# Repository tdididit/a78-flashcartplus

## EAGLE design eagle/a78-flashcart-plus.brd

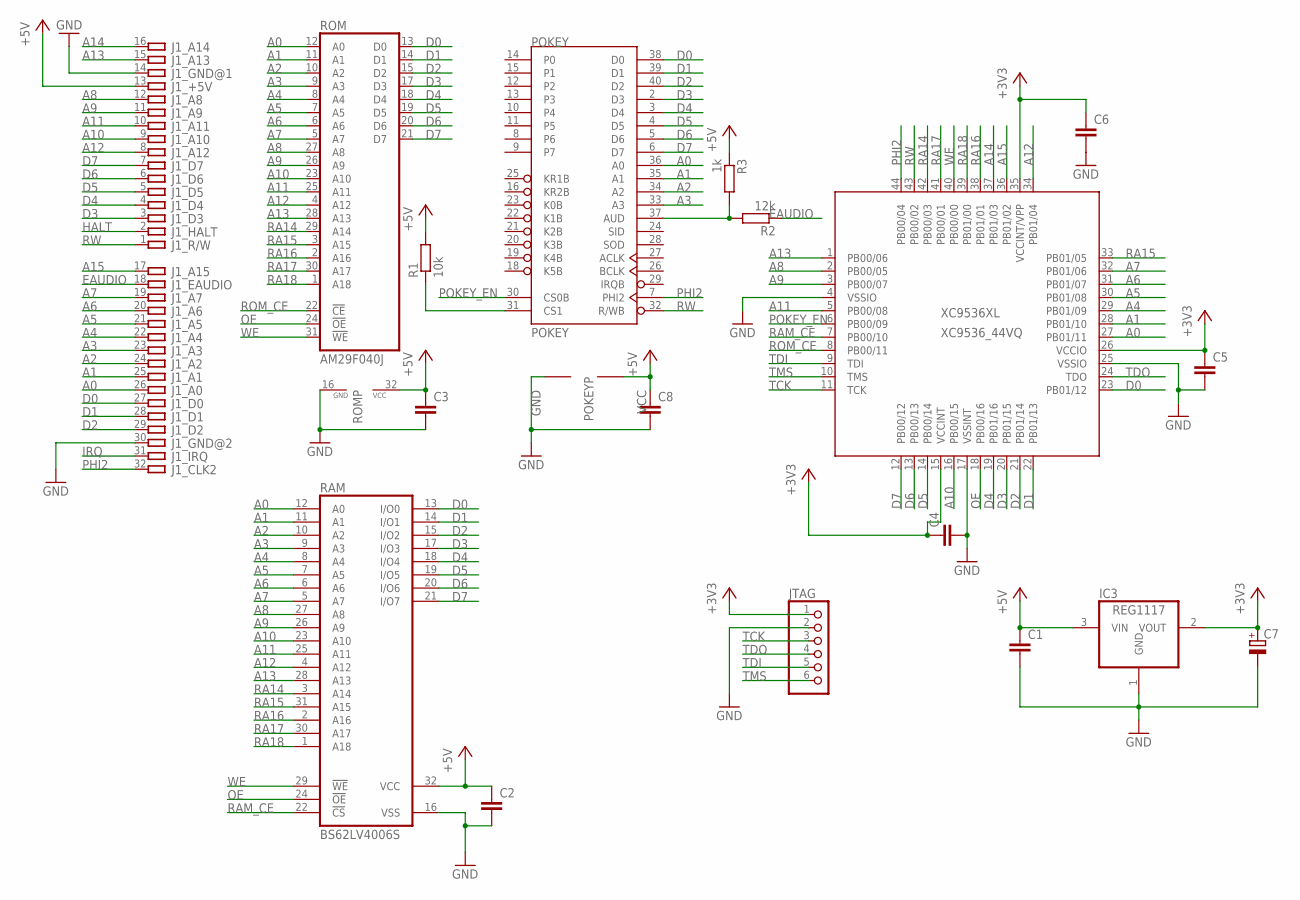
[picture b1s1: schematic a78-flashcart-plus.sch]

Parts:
C1, C2, C3, C4, C5, C6, C8: C-EUC0603; C0603
C7: CPOL-EUSMCC; SMC_C
IC3: REG1117; SOT223
J1: ATARI-7800-LARGE
JTAG: PINHD-1X6; 1X06
POKEY: POKEY; DIL40
R1: 10k; R0603
R2: 12k; R0603
R3: 1k; R0603
RAM: BS62LV4006S; SOP-32
ROM: AM29F040J; PLCC32R
XC9536XL: XC9536_44VQ; SQFP-S-10X10-44

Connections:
+3V3: C4.1, C5.1, C6.1, C7.+, IC3.2 (VOUT), JTAG.1, XC9536XL.15 (VCCINT), XC9536XL.26 (VCCIO), XC9536XL.35 (VCCINT/VPP)
+5V: C1.1, C2.1, C3.1, C8.1, IC3.3 (VIN), J1.13, POKEY.17 (VCC), R1.2, R3.1, RAM.32 (VCC), ROM.32 (VCC)
A0: J1.26, POKEY.36 (A0), RAM.12 (A0), ROM.12 (A0), XC9536XL.27 (PB01/11)
A1: J1.25, POKEY.35 (A1), RAM.11 (A1), ROM.11 (A1), XC9536XL.28 (PB01/10)
A2: J1.24, POKEY.34 (A2), RAM.10 (A2), ROM.10 (A2)
A3: J1.23, POKEY.33 (A3), RAM.9 (A3), ROM.9 (A3)
A4: J1.22, RAM.8 (A4), ROM.8 (A4), XC9536XL.29 (PB01/09)
A5: J1.21, RAM.7 (A5), ROM.7 (A5), XC9536XL.30 (PB01/08)
A6: J1.20, RAM.6 (A6), ROM.6 (A6), XC9536XL.31 (PB01/07)
A7: J1.19, RAM.5 (A7), ROM.5 (A7), XC9536XL.32 (PB01/06)
A8: J1.12, RAM.27 (A8), ROM.27 (A8), XC9536XL.2 (PB00/05)
A9: J1.11, RAM.26 (A9), ROM.26 (A9), XC9536XL.3 (PB00/07)
A10: J1.9, RAM.23 (A10), ROM.23 (A10), XC9536XL.16 (PB00/15)
A11: J1.10, RAM.25 (A11), ROM.25 (A11), XC9536XL.5 (PB00/08)
A12: J1.8, RAM.4 (A12), ROM.4 (A12), XC9536XL.34 (PB01/04)
A13: J1.15, RAM.28 (A13), ROM.28 (A13), XC9536XL.1 (PB00/06)
A14: J1.16, XC9536XL.37 (PB01/03)
A15: J1.17, XC9536XL.36 (PB01/02)
D0: J1.27, POKEY.38 (D0), RAM.13 (I/O0), ROM.13 (D0), XC9536XL.23 (PB01/12)
D1: J1.28, POKEY.39 (D1), RAM.14 (I/O1), ROM.14 (D1), XC9536XL.22 (PB01/13)
D2: J1.29, POKEY.40 (D2), RAM.15 (I/O2), ROM.15 (D2), XC9536XL.21 (PB01/14)
D3: J1.3, POKEY.2 (D3), RAM.17 (I/O3), ROM.17 (D3), XC9536XL.20 (PB01/15)
D4: J1.4, POKEY.3 (D4), RAM.18 (I/O4), ROM.18 (D4), XC9536XL.19 (PB01/16)
D5: J1.5, POKEY.4 (D5), RAM.19 (I/O5), ROM.19 (D5), XC9536XL.14 (PB00/14)
D6: J1.6, POKEY.5 (D6), RAM.20 (I/O6), ROM.20 (D6), XC9536XL.13 (PB00/13)
D7: J1.7, POKEY.6 (D7), RAM.21 (I/O7), ROM.21 (D7), XC9536XL.12 (PB00/12)
DJGJGFJG: POKEY.31 (CS1), R1.1
EAUDIO: J1.18, R2.1
GND: C1.2, C2.2, C3.2, C4.2, C5.2, C6.2, C7.-, C8.2, IC3.1 (GND), J1.14, J1.30, JTAG.2, POKEY.1 (GND), RAM.16 (VSS), ROM.16 (GND), XC9536XL.4 (VSSIO), XC9536XL.17 (VSSINT), XC9536XL.25 (VSSIO)
HALT: J1.2
IRQ: J1.31
unnamed: POKEY.37 (AUD), R2.2, R3.2
OE: RAM.24 (!OE), ROM.24 (!OE), XC9536XL.18 (PB00/16)
PHI2: J1.32, POKEY.7 (PHI2), XC9536XL.44 (PB00/04)
POKEY_EN: POKEY.30 (CS0B), XC9536XL.6 (PB00/09)
RA14: RAM.3 (A14), ROM.29 (A14), XC9536XL.42 (PB00/03)
RA15: RAM.31 (A15), ROM.3 (A15), XC9536XL.33 (PB01/05)
RA16: RAM.2 (A16), ROM.2 (A16), XC9536XL.38 (PB01/01)
RA17: RAM.30 (A17), ROM.30 (A17), XC9536XL.41 (PB00/01)
RA18: RAM.1 (A18), ROM.1 (A18), XC9536XL.39 (PB01/00)
RAM_CE: RAM.22 (!CS), XC9536XL.7 (PB00/10)
ROM_CE: ROM.22 (!CE), XC9536XL.8 (PB00/11)
RW: J1.1, POKEY.32 (R/WB), XC9536XL.43 (PB00/02)
TCK: JTAG.3, XC9536XL.11 (TCK)
TDI: JTAG.5, XC9536XL.9 (TDI)
TDO: JTAG.4, XC9536XL.24 (TDO)
TMS: JTAG.6, XC9536XL.10 (TMS)
WE: RAM.29 (!WE), ROM.31 (!WE), XC9536XL.40 (PB00/00)

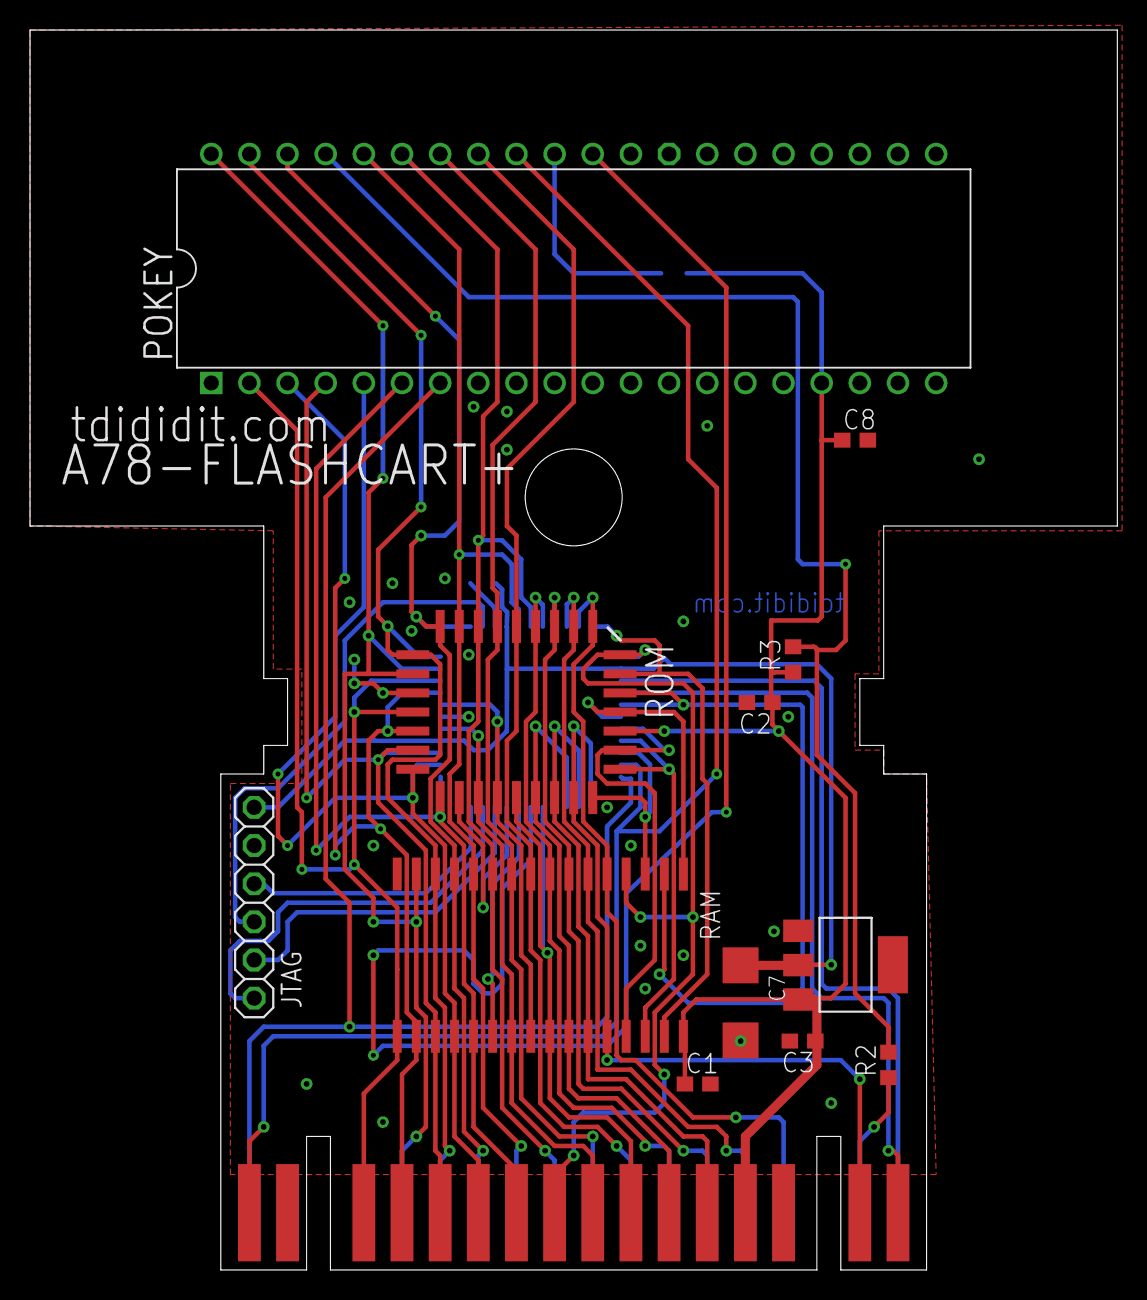
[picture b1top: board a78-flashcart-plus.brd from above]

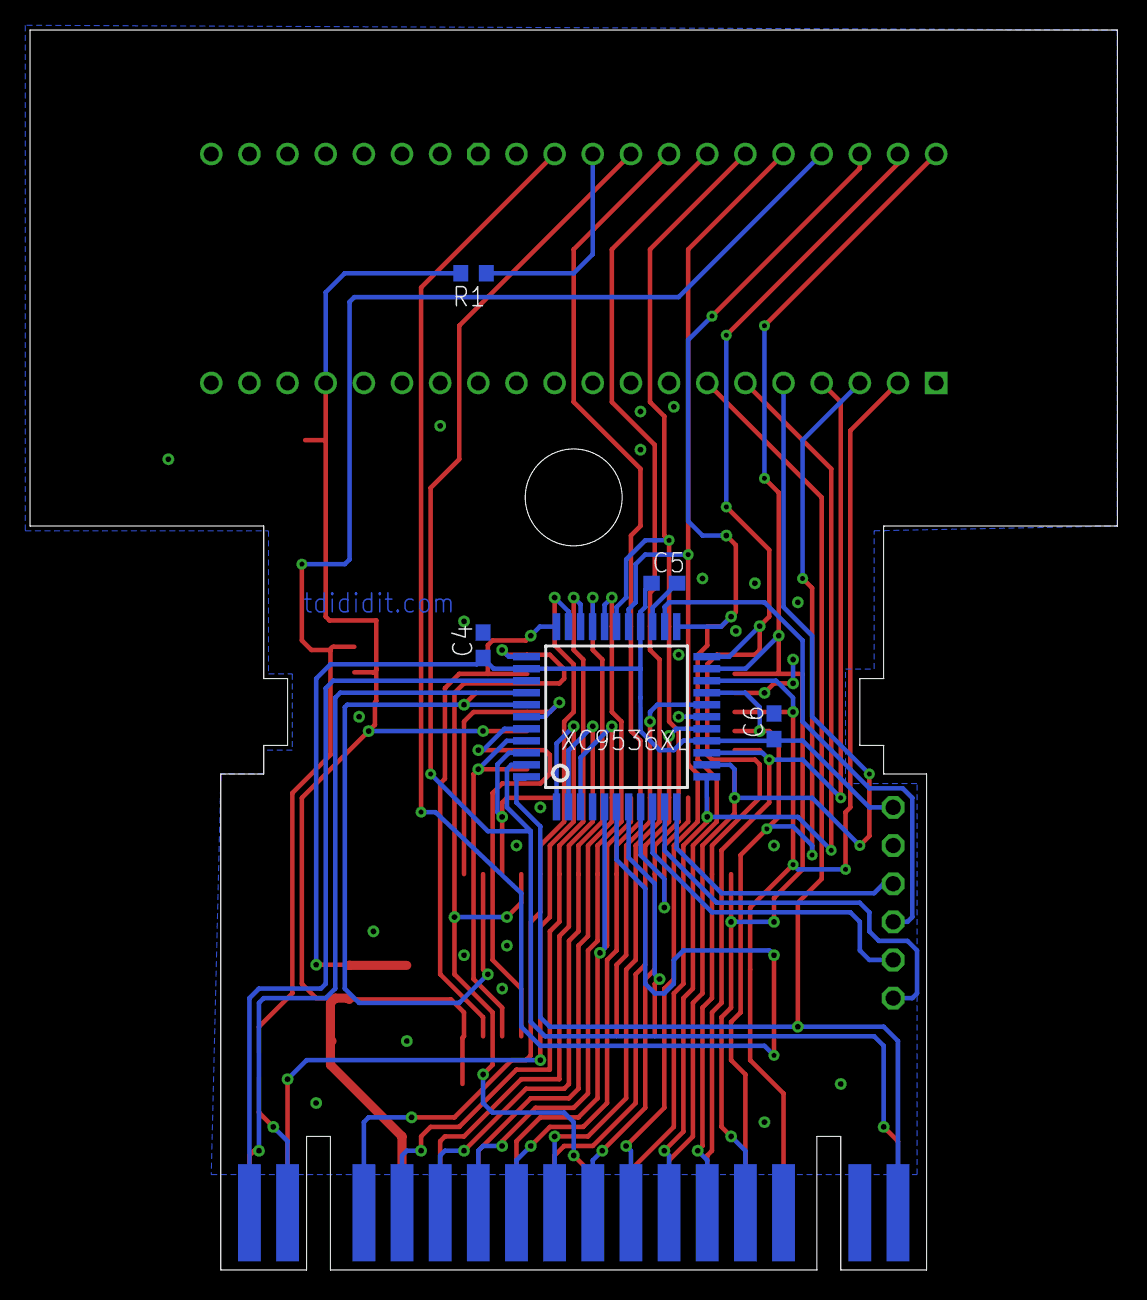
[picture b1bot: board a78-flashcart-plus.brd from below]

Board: 2 copper layers, 72.4 x 82.5 mm, 18 parts (5 on the bottom side), 46 nets.

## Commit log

2016-03-03 :octocat: Added .gitattributes
2016-03-21 update of eagle and sketchup files
